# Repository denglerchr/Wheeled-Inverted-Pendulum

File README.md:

# Wheeled-Inverted-Pendulum
## Description
This repo contains the required resources to build and deploy a relatively inexpensive wheeled inverted pendulum. It was build to provide an easily upgradable and programmable test-bed for control algorithms. The final robot can be programmed in python and accesses via wifi. It can compute computationally heavy (-> compared to other stuff done in control community) control algorithms on the raspberry pi, e.g. evaluate a neural network of mediocre size.

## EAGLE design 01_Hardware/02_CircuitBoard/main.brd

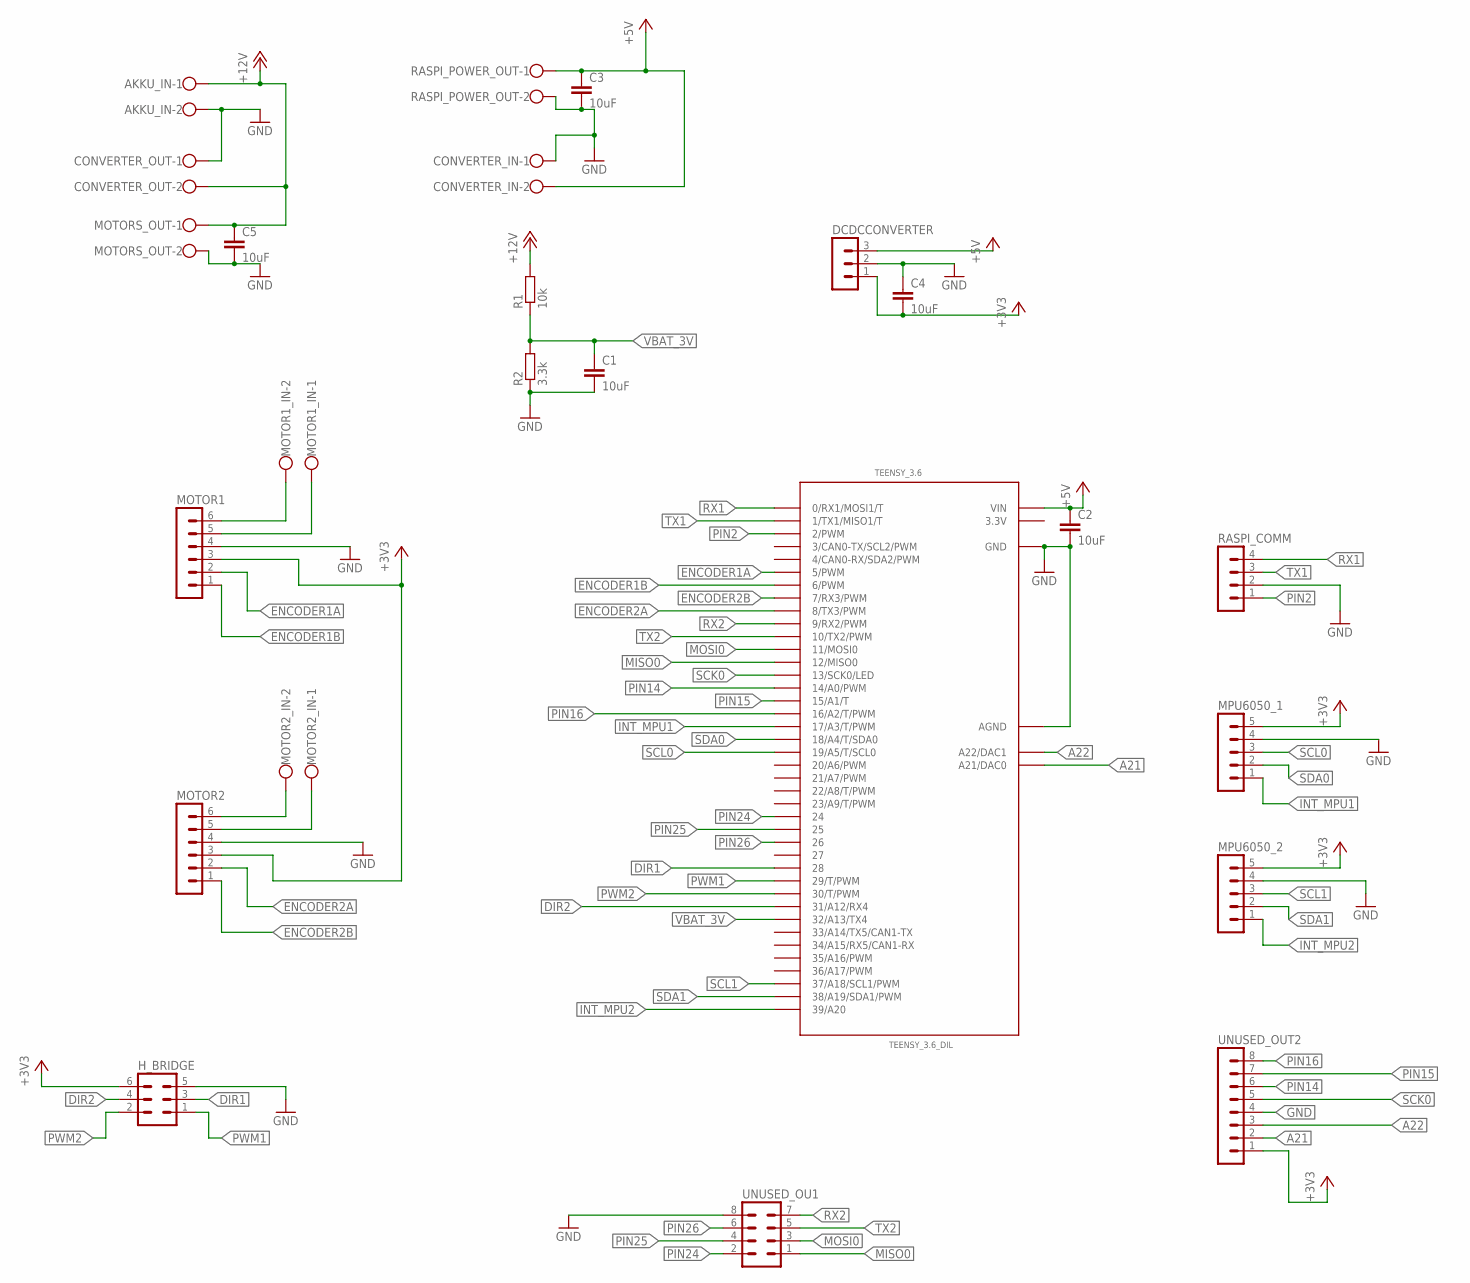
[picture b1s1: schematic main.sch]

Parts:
AKKU_IN: W237-102
C1, C2, C3, C4, C5: 10uF; C1206
CONVERTER_IN: W237-102
CONVERTER_OUT: W237-102
DCDCCONVERTER: MA03-1
H_BRIDGE: MA03-2
MOTOR1, MOTOR2: MA06-1
MOTOR1_IN, MOTOR2_IN: W237-102
MOTORS_OUT: W237-102
MPU6050_1, MPU6050_2: MA05-1
R1: 10k; R1206
R2: 3.3k; R1206
RASPI_COMM: MA04-1
RASPI_POWER_OUT: W237-102
TEENSY_3.6: TEENSY_3.6_DIL
UNUSED_OU1: MA04-2
UNUSED_OUT2: MA08-1

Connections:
3.3V: TEENSY_3.6.3.3V, TEENSY_3.6.3.3V3 (3.3V)
+3V3: C4.2, DCDCCONVERTER.1, H_BRIDGE.6, MOTOR1.3, MOTOR2.3, MPU6050_1.5, MPU6050_2.5, UNUSED_OUT2.1
+5V: C2.1, C3.1, CONVERTER_IN.2, DCDCCONVERTER.3, RASPI_POWER_OUT.1, TEENSY_3.6.VIN
+12V: AKKU_IN.1, C5.1, CONVERTER_OUT.2, MOTORS_OUT.1, R1.2
A21: TEENSY_3.6.A21 (A21/DAC0), UNUSED_OUT2.2
A22: TEENSY_3.6.A22 (A22/DAC1), UNUSED_OUT2.3
DIR1: H_BRIDGE.3, TEENSY_3.6.28
DIR2: H_BRIDGE.4, TEENSY_3.6.31/A12 (31/A12/RX4)
ENCODER1A: MOTOR1.2, TEENSY_3.6.5 (5/PWM)
ENCODER1B: MOTOR1.1, TEENSY_3.6.6 (6/PWM)
ENCODER2A: MOTOR2.2, TEENSY_3.6.8 (8/TX3/PWM)
ENCODER2B: MOTOR2.1, TEENSY_3.6.7 (7/RX3/PWM)
GND: AKKU_IN.2, C1.2, C2.2, C3.2, C4.1, C5.2, CONVERTER_IN.1, CONVERTER_OUT.1, DCDCCONVERTER.2, H_BRIDGE.5, MOTOR1.4, MOTOR2.4, MOTORS_OUT.2, MPU6050_1.4, MPU6050_2.4, R2.1, RASPI_COMM.2, RASPI_POWER_OUT.2, TEENSY_3.6.AGND, TEENSY_3.6.GND, TEENSY_3.6.GND1 (GND), UNUSED_OU1.8, UNUSED_OUT2.4
INT_MPU1: MPU6050_1.1, TEENSY_3.6.17/A3 (17/A3/T/PWM)
INT_MPU2: MPU6050_2.1, TEENSY_3.6.39/A20
MISO0: TEENSY_3.6.12 (12/MISO0), UNUSED_OU1.1
MOSI0: TEENSY_3.6.11 (11/MOSI0), UNUSED_OU1.3
MOTOR1+: MOTOR1.6, MOTOR1_IN.2
MOTOR1-: MOTOR1.5, MOTOR1_IN.1
MOTOR2+: MOTOR2.6, MOTOR2_IN.2
MOTOR2-: MOTOR2.5, MOTOR2_IN.1
PIN2: RASPI_COMM.1, TEENSY_3.6.2 (2/PWM)
PIN14: TEENSY_3.6.14/A0 (14/A0/PWM), UNUSED_OUT2.6
PIN15: TEENSY_3.6.15/A1 (15/A1/T), UNUSED_OUT2.7
PIN16: TEENSY_3.6.16/A2 (16/A2/T/PWM), UNUSED_OUT2.8
PIN24: TEENSY_3.6.24, UNUSED_OU1.2
PIN25: TEENSY_3.6.25, UNUSED_OU1.4
PIN26: TEENSY_3.6.26, UNUSED_OU1.6
PWM1: H_BRIDGE.1, TEENSY_3.6.29 (29/T/PWM)
PWM2: H_BRIDGE.2, TEENSY_3.6.30 (30/T/PWM)
RX1: RASPI_COMM.4, TEENSY_3.6.0 (0/RX1/MOSI1/T)
RX2: TEENSY_3.6.9 (9/RX2/PWM), UNUSED_OU1.7
SCK0: TEENSY_3.6.13 (13/SCK0/LED), UNUSED_OUT2.5
SCL0: MPU6050_1.3, TEENSY_3.6.19/A5 (19/A5/T/SCL0)
SCL1: MPU6050_2.3, TEENSY_3.6.37/A18 (37/A18/SCL1/PWM)
SDA0: MPU6050_1.2, TEENSY_3.6.18/A4 (18/A4/T/SDA0)
SDA1: MPU6050_2.2, TEENSY_3.6.38/A19 (38/A19/SDA1/PWM)
TX1: RASPI_COMM.3, TEENSY_3.6.1 (1/TX1/MISO1/T)
TX2: TEENSY_3.6.10 (10/TX2/PWM), UNUSED_OU1.5
VBAT_3V: C1.1, R1.1, R2.2, TEENSY_3.6.32/A13 (32/A13/TX4)

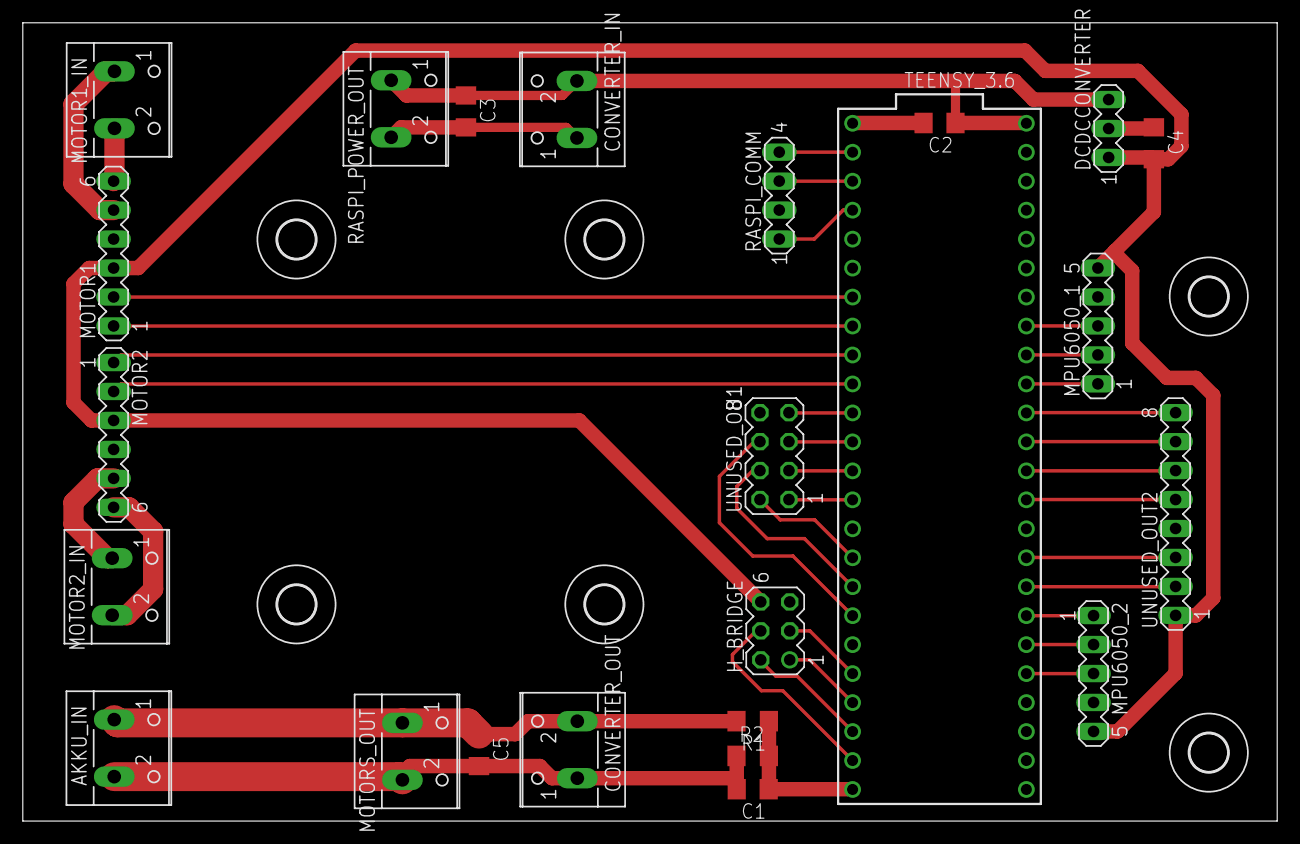
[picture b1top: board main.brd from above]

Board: 2 copper layers, 110.0 x 70.0 mm, 30 parts (0 on the bottom side), 40 nets.

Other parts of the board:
U$1, U$2, U$3, U$4, U$5, U$6: 3,3

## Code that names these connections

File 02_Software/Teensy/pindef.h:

#define PIN_RED_LED 13

// For the Raspberry Pi
#define RASPBERRY_SERIAL Serial1

// MPU interrupt pins
#define PIN_MPU_INTERRUPT 17

//Encoder pins
#define PIN_ENCODER1A 7
#define PIN_ENCODER1B 8
#define PIN_ENCODER2A 5
#define PIN_ENCODER2B 6

// Motor pins (MOTOR1 is right side and controlled by u[1])
#define PIN_PWM_LEFT 30
#define PIN_DIR_LEFT 31
#define PIN_PWM_RIGHT 29
#define PIN_DIR_RIGHT 28

//Akku voltage pin
#define PIN_AKKU_ANALOG 32

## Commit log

2018-12-05 Added Image in the documentation
2018-12-05 Update README again
2019-06-03 Add model file
2019-06-03 Correct type used from float to binaryFloat
2019-06-04 Update model to a tested and working version
2019-06-04 Update to first version that could actually run
2019-06-17 Fix the state to start at 0, and update model thresholds
2020-06-02 Update Doc and Readme, comment PC communication in the Main Teensy File
2020-06-02 Add Table of content and recreate PDF
